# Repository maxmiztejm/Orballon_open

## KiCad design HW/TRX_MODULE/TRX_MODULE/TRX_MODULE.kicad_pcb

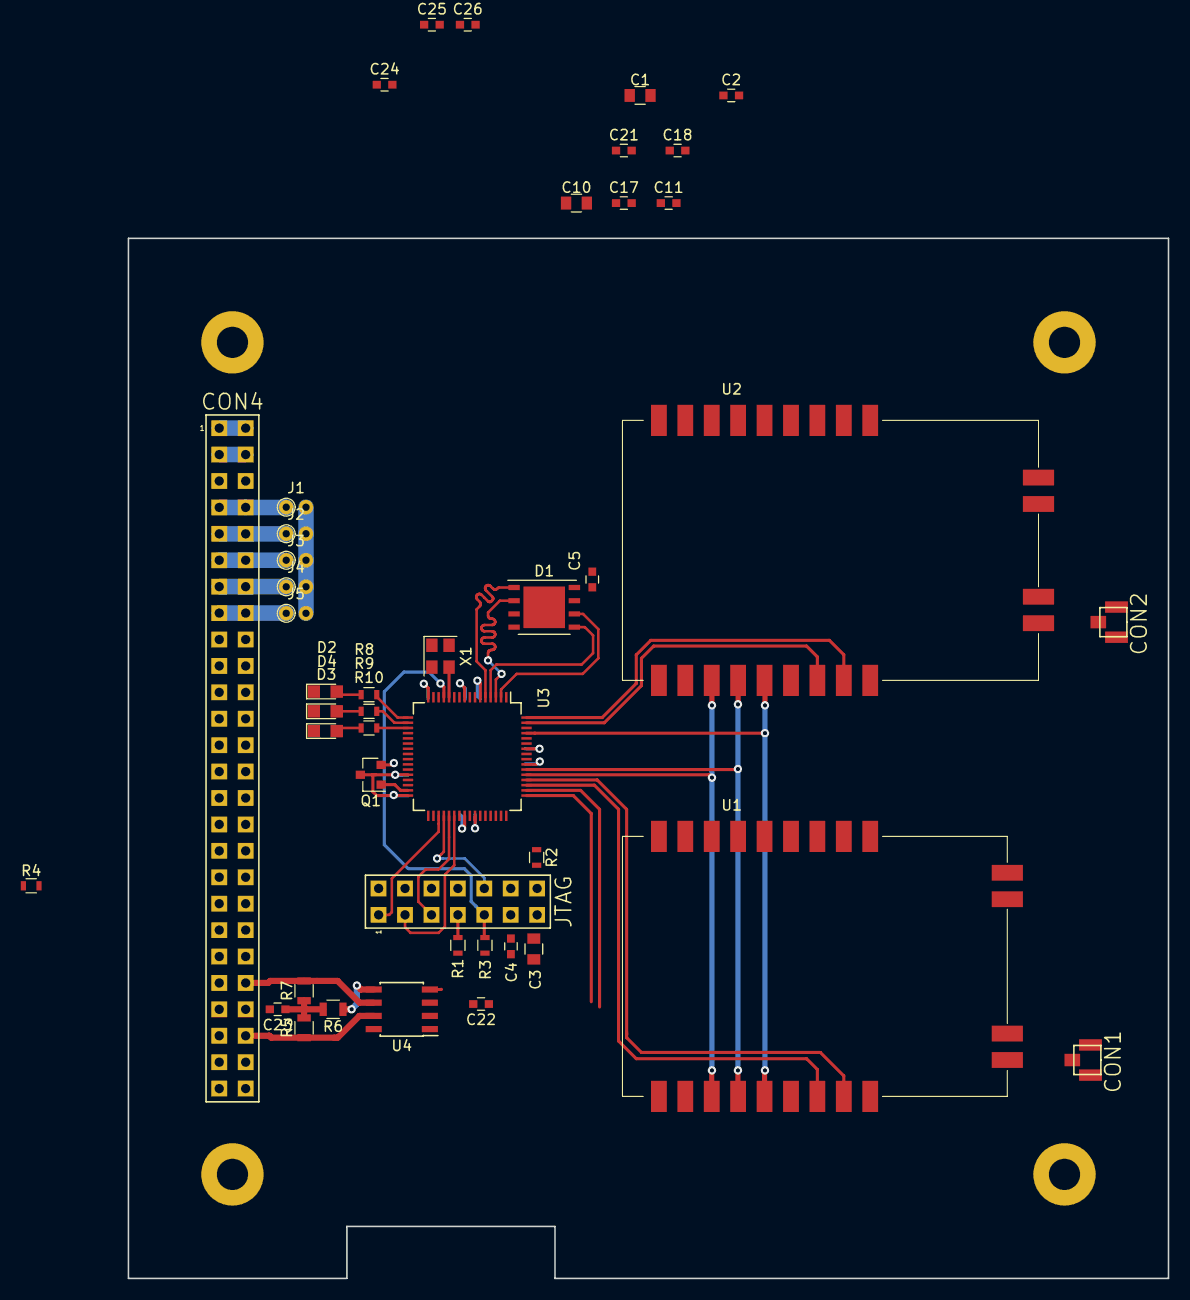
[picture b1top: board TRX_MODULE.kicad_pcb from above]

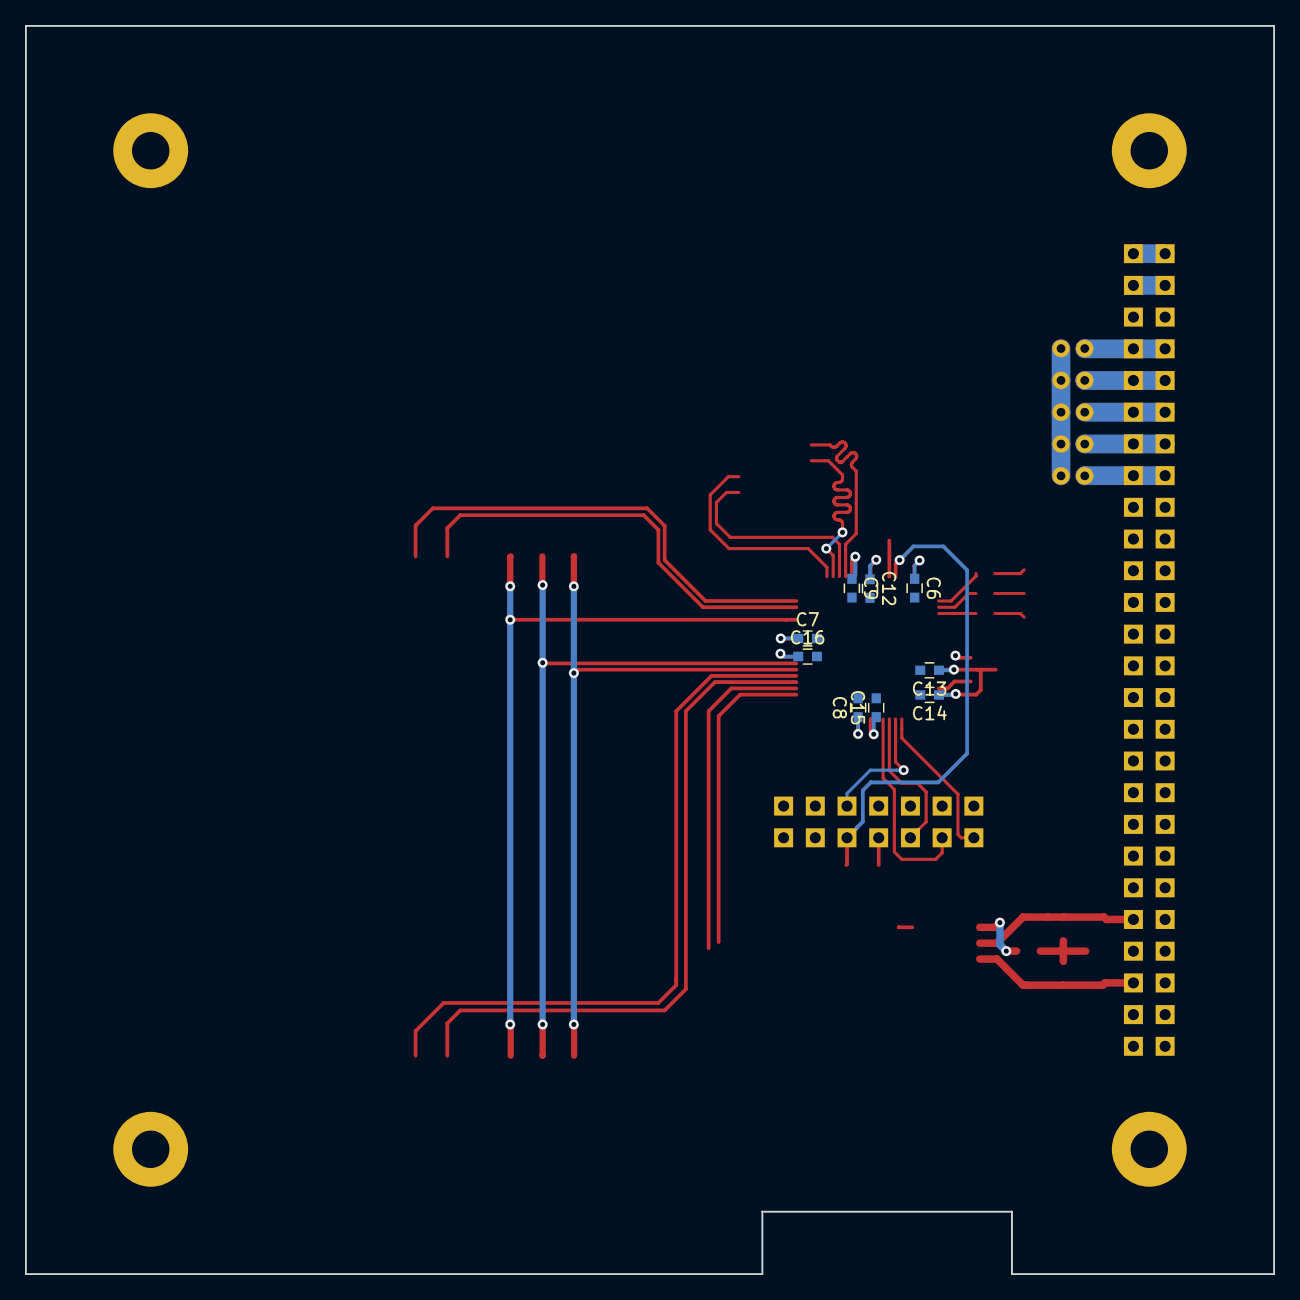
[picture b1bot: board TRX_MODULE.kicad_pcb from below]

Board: 2 copper layers, 100.0 x 100.0 mm, 57 parts (9 on the bottom side), 47 nets.

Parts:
C1, C3, C10: ?; C_0805
C2, C4, C11: ?; C_0603
C5, C6, C7, C8, C9, C12, C13, C14, C15, C16, C17, C21, C22, C24, C25: 100nF; C_0603
C18: 120nF; C_0603
C23: 4700pF; C_0603
C26: 10uF; C_0603
CON1, CON2: Conn_Coaxial; CONN-RF-UFL
CON4: HEADER_2x26; Straight_2x26
CON5: JTAG; Straight_2x07
D1: FM25V20A; DFN-8-1EP_6x5mm_Pitch1.27mm_LargeFlag
D2, D3, D4: LED; LED_0805
J1, J2, J3, J4, J5: 0; R_Axial_DIN0204_L3.6mm_D1.6mm_P1.90mm_Vertical
M1, M2, M3, M4: HOLE; MountingHole_3mm
Q1: BC817; SOT-23
R1, R2, R3, R4, R8, R9, R10: 10k; R_0603
R5, R7: 60; R_0805
R6: 300; R_0805
U1: E19-433M30S; E19-433MS1W
U2: E19-868M30S; E19-868MS1W
U3: SPC560P34L1; LQFP-64_10x10mm_Pitch0.5mm
U4: MCP2561; SOIC-8_3.9x4.9mm_Pitch1.27mm
X1: ASE-xxxMHz; Oscillator_SMD_Abracon_ASE-4pin_3.2x2.5mm

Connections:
1PPS: CON4.52, U3.8
+1V2: C6.1, C7.1, C8.1, C18.1, Q1.2, U3.16, U3.42, U3.58
+3V3: C3.1, C4.1, C5.1, C9.1, C12.1, C13.1, C14.1, C15.1, C16.1, C17.2, C25.2, C26.2, CON5.11, D1.8, Q1.3, R1.2, R3.2, R4.1, U3.6, U3.9, U3.28, U3.32, U3.40, U3.55, X1.1, X1.4
+5V: C1.2, C2.2, C10.2, C11.2, C22.2, C24.1, J1.2, J2.2, J3.2, J4.2, J5.2, U1.11, U2.11, U4.3
+5V_A: CON4.7, CON4.8, J1.1
+5V_B: CON4.9, CON4.10, J2.1
+5V_C: CON4.11, CON4.12, J3.1
+5V_D: CON4.13, CON4.14, J4.1
+5V_E: CON4.15, CON4.16, J5.1
+12V_A: CON4.1, CON4.2
+12V_B: CON4.3, CON4.4
/CAN_RX: U3.50, U4.4
/CAN_STBY: U3.48, U4.8
/CAN_TX: U3.49, U4.1
/CS_0: D1.1, U3.5
/MISO_0: D1.2, U3.3
/MISO_1: U1.13, U2.13, U3.54
/MOSI_0: D1.5, U3.4
/MOSI_1: U1.14, U2.14, U3.61
/RXEN_1: U2.17, U3.64
/RXEN_2: U1.17, U3.52
/SCK_0: D1.6, U3.2
/SCK_1: U1.12, U2.12, U3.53
/TXEN_1: U2.16, U3.63
/TXEN_2: U1.16, U3.51
CAN_H: CON4.48, R5.1, U4.7
CAN_L: CON4.44, R7.2, U4.6
GND: C1.1, C2.1, C3.2, C4.2, C5.2, C6.2, C7.2, C8.2, C9.2, C10.1, C11.1, C12.2, C13.2, C14.2, C15.2, C16.2, C17.1, C18.2, C21.1, C22.1, C23.2, C24.2, C25.1, C26.1, CON1.2, CON2.2, CON4.5, CON4.6, CON4.17, CON4.18, CON4.21, CON4.22, CON4.45, CON4.46, CON4.49, CON4.50, CON5.2, CON5.4, CON5.6, CON5.12, D1.4, D2.1, D3.1, D4.1, M1.1, M2.1, M3.1, M4.1, R2.1, U1.1, U1.9, U1.10, U1.18, U1.20, U1.21, U1.22, U2.1, U2.9, U2.10, U2.18, U2.20, U2.21, U2.22, U3.7, U3.10, U3.15, U3.29, U3.39, U3.43, U3.47, U3.56, U3.59, U4.2, X1.2
unnamed: C23.1, R5.2, R6.2, R7.1
unnamed: CON1.1, U1.19
unnamed: CON2.1, U2.19
unnamed: CON5.7, R1.1
unnamed: CON5.14, R2.2
unnamed: D2.2, R8.1
unnamed: D3.2, R10.1
unnamed: D4.2, R9.1
unnamed: Q1.1, U3.31
unnamed: R6.1, U4.5
unnamed: R8.2, U3.17
unnamed: R9.2, U3.18
unnamed: R10.2, U3.19
unnamed: U3.12, X1.3
RESET: C21.2, CON5.9, R3.1, R4.2, U3.13
TCKOUT: CON5.5, U3.37
TDI: CON5.1, U3.35
TDO: CON5.3, U3.38
TMS: CON5.10, U3.36
